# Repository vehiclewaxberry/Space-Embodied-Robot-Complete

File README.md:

# 航天服务星具身智能机械臂机器人

**Space Service Robot with Embodied Intelligence**

面向在轨服务的 12U 立方星服务星 + B601 六自由度机械臂的完整数字样机、机械/电气设计与自由漂浮动力学证据库。

*A complete digital prototype, mechanical/electrical design package, and free-floating dynamics evidence base for a 12U CubeSat servicing spacecraft with a B601 6-DOF manipulator.*

---

## 项目定位 / Scope

这是一个**在轨服务空间机器人学的科研项目**，同时承载长期硬件研发。两条线互为约束：

- **研究线** —— 面向抓取后可稳定性的**预见式具身抓取**。核心问题：在自由漂浮、刚柔耦合、目标非合作的条件下，捕获策略的可行域由哪些物理边界决定。
- **工程线** —— 可装配、可参数化、可验证的 12U 服务星与 B601 机械设计，作为研究结论的物理载体与参数来源。

研究产出以**机器裁决证据**（`*_gate_check.json`）与论文结构为组织形式，而非演示件。论文规划入口见 [`10_research/paper1_architecture.md`](10_research/paper1_architecture.md)（Paper 1 = 柔性耦合捕获任务可行域），问题树见 [`10_research/research_questions/`](10_research/research_questions/)。

*This is a research project in on-orbit-servicing space robotics, carried alongside long-term hardware development. The research line studies predictive embodied grasping for post-capture stabilizability — specifically, which physical boundaries determine the feasible domain of capture strategies under free-floating, rigid-flexible coupled, non-cooperative conditions. Outputs are organised as machine-adjudicated evidence and paper structure, not demos.*

> **关于历史来源**：项目起源于中国研究生未来飞行器创新大赛（第十二届）。比赛记录、机器 Gate 与负结果作为**历史证据**原位保留，但**比赛期限与比赛交付不再构成研究议程、工程验收门槛或授权 Gate**。请勿据历史比赛记录升级当前结论。

### 任务设定 / Mission

| 项 | 值 |
|---|---|
| 服务星 | 12U CubeSat 平台 |
| 机械臂 | B601，6R 串联构型 |
| 目标 A | 150 kg 翻滚空间碎片 |
| 目标 B | 22 kg 非合作目标星 |
| 动力学工况 | 自由漂浮（free-floating），基座不固定 |
| 研究线 | 面向抓取后可稳定性的预见式具身抓取 |

---

## 仓库导航 / Repository layout

八个业务域，根目录不再建立平行的 `src/` `docs/` `results/` 树。

| 目录 | 内容 |
|---|---|
| [`01_project/`](01_project/) | 项目入口、治理、协作原件、历次工作包记录 |
| [`10_research/`](10_research/) | 研究问题树、方法、合同、知识库、论文材料 |
| [`20_engineering/`](20_engineering/) | **CAD、电气、BOM、参数、接口与设计证据** |
| [`30_simulation/`](30_simulation/) | 模型、程序、测试、原始结果、机器裁决 |
| [`40_evidence/`](40_evidence/) | 图表、媒体、离线展示 |
| [`50_literature/`](50_literature/) | 题录、阅读卡、BibTeX |
| [`70_tools/`](70_tools/) | 编目、展示、校验工具 |
| [`80_third_party/`](80_third_party/) | 外部来源登记与许可（见 [NOTICE.md](NOTICE.md)） |

全项目导航入口：**[PROJECT_MAP.md](PROJECT_MAP.md)**

---

## 协作者快速上手 / Getting started for collaborators

仓库含 **13 GB Git LFS 内容**（7,328 个对象，主要是 CAD）。**克隆方式选错会出问题**，请按下面来。

### ① 先装 Git LFS —— 不装的话你拿到的是一堆占位符

这是最常见的坑：没装 LFS 就 `git clone`，所有 CAD 文件会变成约 130 字节的指针文本。**文件名看着都在，但一个都打不开。**

```bash
git lfs install
```

*Install [Git LFS](https://git-lfs.com/) first. Without it every CAD file clones as a ~130-byte pointer stub — the filenames all look right, but nothing opens.*

### ② 推荐：先不拉 CAD，按需取件

完整克隆会下载 13 GB，**消耗仓库的 LFS 带宽配额**；配额耗尽后**所有人**的 LFS 下载都会被阻断。除非确实需要全部 CAD，否则请用：

```bash
GIT_LFS_SKIP_SMUDGE=1 git clone https://github.com/vehiclewaxberry/Space-Embodied-Robot-Complete.git
```

这样能拿到全部代码、文档、仿真结果与机器裁决（约 256 MB），CAD 先留作指针。需要某个具体部件时再单独拉：

```bash
# 例：只取最新整星总装
git lfs pull --include="20_engineering/SERVICE_STAR_CORE_INSTALLATION_R6H_20260920/**"

# 例：只取某一批 STEP
git lfs pull --include="20_engineering/SERVICE_STAR_HARDWARE_COMPACT_20260921/**"
```

*Full clones pull 13 GB and consume the repository's shared LFS bandwidth quota; once it is exhausted, LFS downloads are blocked for everyone. Prefer the skip-smudge clone above and fetch only what you need.*

### ③ 确实需要全部 CAD 时

```bash
git clone https://github.com/vehiclewaxberry/Space-Embodied-Robot-Complete.git
```

请先知会仓库所有者——这一次操作会占用约 13 GB 带宽配额。

### 打开 CAD 需要什么

| 格式 | 仓库内文件数 | 需要的软件 |
|---|---|---|
| `.STEP` | 3,404 | **任意 CAD 软件**（FreeCAD、Fusion、CATIA、NX…）— 没有 SolidWorks 就用这个 |
| `.SLDASM` / `.SLDPRT` | 6,233 | SolidWorks 2024 及以上 |
| `.FCStd` | 89 | FreeCAD |
| `.glb` / `.stl` | 873 | 任意三维查看器（仅可视化，非设计源） |

全部 CAD 合计 13 GB LFS（7,328 个去重对象——同内容的文件共享一份存储，所以实际下载量小于按文件数的估计）。

---

## 研究线 / Research programme

### 六层架构

研究按六层组织，**各层分别取证，不由某层结论覆盖其它层**：

| 层 | 职责 | 状态 |
|---|---|---|
| **L0** | 任务可行性 / 策略 | 已实现（`sim_10`、`sim_12`） |
| **L1** | SAFE 证据核 | `SAFE-00` 47/47 PASS，`review_status=PENDING_REVIEW` |
| **L2** | 确定性控制 | `CTRL-01/02`，带 PROVISIONAL 范围限定 |
| **L3** | 刚柔世界模型 | `sim_11` v1.1，含占位参数 |
| **L4** | 具身候选生成 | 规划态，未实施 |
| **L5** | 地面验证 | H0–H3 规划态，未实施 |

导航：[`10_research/00_project_architecture/`](10_research/00_project_architecture/)

### 论文线

| 论文 | 主题 | 状态 |
|---|---|---|
| **Paper 1** | 柔性耦合捕获任务可行域 | 证据/查新收口中，结构见 [`paper1_architecture.md`](10_research/paper1_architecture.md) |
| **Paper 2** | 接触带宽 / 保真度 | 候选，未启动 |

问题树 Q1–Q6、理论假设与主张-证据关系见 [`10_research/research_questions/`](10_research/research_questions/)、[`theory_graph/`](10_research/theory_graph/)、[`contribution_map/`](10_research/contribution_map/)。

文献主清单：[`50_literature/references/manifest.yaml`](50_literature/references/manifest.yaml)（44 篇 PDF / 29 张阅读卡；**PDF 全文因版权不随仓库分发**，按 manifest 自行获取）。

### 规划态支线（**尚未授权实施**）

`BRIDGE-UT` 带界不确定目标操作、`Q6-L1` 预制接口装配、On-Orbit Assembly Wave A、Physics-Gated Agent、ROM、VLA —— 这些目录存在**不等于**实施完成或已授权。请按各目录内的具名合同理解其范围。

---

## 当前硬件基线 / Current hardware baseline

这是接手后续开发时**首先要看的**部分。

| 要做的事 | 入口 |
|---|---|
| 四系统硬件主设计（机械 / 电气线束 / 能源热控 / 动力推进） | [`20_engineering/SERVICE_STAR_HARDWARE_COMPACT_20260921/`](20_engineering/SERVICE_STAR_HARDWARE_COMPACT_20260921/) |
| **最新整星总装（数字样机）** | [`SERVICE_STAR_CORE_INSTALLATION_R6H_20260920/native/SERVICE_STAR_SERVICE_R6H.SLDASM`](20_engineering/SERVICE_STAR_CORE_INSTALLATION_R6H_20260920/native/) |
| 电气选型当前指针 | [`20_engineering/SERVICE_STAR_ELECTRICAL_LATEST.json`](20_engineering/SERVICE_STAR_ELECTRICAL_LATEST.json) |
| R7 安装布局草案（**未完成项**） | [`20_engineering/SERVICE_STAR_AUX_STOP_INSTALLATION_R7_20260921/`](20_engineering/SERVICE_STAR_AUX_STOP_INSTALLATION_R7_20260921/) |
| 上游机械来源（星体本体） | [`20_engineering/service_robot_wp03_spacecraft_body_r1/`](20_engineering/service_robot_wp03_spacecraft_body_r1/) |

**读法约定**：选型候选与未安装草案分别看待，**不按目录日期推定完工**。R6H 原件保留，没有回退为早期 WP03。

### CAD 格式说明

原生件为 SolidWorks（`.SLDPRT` / `.SLDASM`），中性交换格式为 `.STEP`，二者均通过 Git LFS 存储。**克隆方式与所需软件见上文[协作者快速上手](#协作者快速上手--getting-started-for-collaborators)**——直接 `git clone` 而未装 LFS 会拿到占位符而非真实 CAD。

---

## 已验证的核心结果 / Verified results

以下数值来自各模块的**机器裁决 JSON**（`*_gate_check.json`），引用时请勿改动。注意：**测试 PASS ≠ 科学 Gate PASS**。

| 编号 | 结论 | 关键数值 |
|---|---|---|
| `sim_05` | B601 自由漂浮，臂运动致基座姿态扰动 | 峰值 **19.20°**；动量守恒 7.3e-17 |
| `sim_06` | 矢量式捕获冲量——**捕获 ≠ 消旋** | 碎片 @3°/s → 捕获后 3.06°/s |
| `sim_07` | ANCF 柔性帆板，点捕获激振 vs 刚性锁定 | ≈ **92×**；振铃 37–75 s |
| `sim_08` | 150 kg 碎片消旋**必须用推力器** | `\|H_c\|` = 3.65 N·m·s = **12×** 轮组容量 |
| `sim_10` | 任务可行域 9000 点四门 fail-closed 扫描 | 裁决 `SIM10_GATES_PASS` |
| `sim_11` v1.1 | 刚柔耦合，有限接触窗口 | `SIM11_GATES_PASS_WITH_PROVISIONAL_PARAMS` |
| `sim_12` Phase1 | 16 例策略证明集——**最优捕获策略是 binding gate 的函数** | `SIM12_PHASE1_GATES_PASS` |
| `SAFE-00` | 运行时安全门 | 47/47 PASS，七绕过面全封 |

### 对后续在轨服务开发的直接含义

1. **基座扰动不可忽略**：自由漂浮下 19.20° 的姿态耦合意味着臂规划必须与姿态控制联合求解。
2. **捕获与消旋是两个问题**：捕获冲量不消除目标角动量；150 kg 级目标的消旋超出轮组容量一个数量级。
3. **柔性帆板是激振主源**：点捕获相对刚性锁定放大约 92 倍，接触策略必须考虑帆板模态。
4. **策略选择依赖于约束边界**：不同 binding gate 下最优策略不同（S1 / S3a / ABORT）。

---

## 明确的未完成项与占位参数 / Known gaps

本节是**刻意保留**的。项目约定：负结果、UNKNOWN 与占位参数不得被整理或总结所掩盖。

| 项 | 状态 | 影响 |
|---|---|---|
| **帆板质量 0.348 kg** | **占位值**。真实面密度 2–5 kg/m²，差 5–10 倍 | 真实参数下「柔性反馈可忽略」的结论**可能翻转**。当前最大硬伤 |
| **接触窗口 `T_c` = 20 ms** | `PROVISIONAL`，待 B601 夹爪实测 | 需替换 `scene_A2_capture.yaml` 后重跑带宽口径 Gate |
| 帆板模态参数 | 占位 | 同上 |
| `e15` ANCF 认证 | 交叉求解最大差 5.64% > 5% 门槛 → `REPEAT_ANCF_CERTIFICATION` | 全耦合新模型须重过该 Gate |
| `FLEX` | `UNKNOWN`，不入 `sim_10` 判据 | 可行域为**刚体边界** |
| R7 安装布局 | 草案，未安装 | 不得按日期推定完工 |
| `CTRL-02` 姿态分账 | `PASS_WITH_PROVISIONAL_SCOPE` | 硬件有效稳定性 `NOT_EVALUATED_NO_ACTUATOR_DYNAMICS` |

> 引用控制类结论时必须带限定语：「**在冻结增益与预注册轨迹下**」。

---

## 证据与结论约定 / Evidence conventions

这套约定是项目的核心工程文化，接手者请遵守：

- **科学结论只认机器裁决 JSON**（`*_gate_check.json`），不认文档摘要。
- **测试通过 ≠ 科学 Gate 通过**。
- 每个 `sim_XX` / `eXX` 模块自带 `src/` `tests/` `results/` `docs/`，自包含。
- 失败、`UNKNOWN`、受限结果**留在原拥有者目录**，不被后续工作覆盖。
- 不同模型与版本的结果**不互相覆盖**，导航不汇总为单一通过状态。
- 目录同名、同日期或位于 `archive/` `_work/` **不足以证明文件无用**。

---

## 复现 / Reproducing

各仿真模块自包含。典型流程：

```bash
cd 30_simulation/sim_11_coupled_dynamics
python -m pytest tests/          # 模块测试
python src/run_all.py            # 重跑场景与 Gate
cat results/sim_11_gate_check.json   # 读机器裁决
```

> **注意**：`control_01` / `control_02` 的 `run_all.py` 会**覆写** `results/` 下的 gate JSON。运行前请先 snapshot，运行后 restore。

---

## 第三方 / Third-party

本仓库**不转发**上游第三方代码库。所使用的外部平台（Basilisk、Exudyn、Chrono、SPART、SpaceDyn、Astrobee、OpenVLA、openpi 等）及其许可证登记于 **[NOTICE.md](NOTICE.md)**，请从各自上游获取。

外部参考 CAD 与供应商模型的来源、版本与许可见 [`80_third_party/README.md`](80_third_party/README.md)。

---

## 引用 / Citation

见 [CITATION.cff](CITATION.cff)。

---

## 许可 / License

见 [LICENSE](LICENSE)。第三方组件各自适用其上游许可，见 [NOTICE.md](NOTICE.md)。

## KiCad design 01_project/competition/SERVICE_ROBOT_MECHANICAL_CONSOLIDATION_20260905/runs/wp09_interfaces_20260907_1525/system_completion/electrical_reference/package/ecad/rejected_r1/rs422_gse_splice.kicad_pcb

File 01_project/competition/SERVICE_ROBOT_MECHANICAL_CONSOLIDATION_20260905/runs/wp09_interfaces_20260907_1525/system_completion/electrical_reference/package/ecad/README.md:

# 原生电气接口候选

已实际生成并用 KiCad10.0.6 读取两套原生设计：

- [直流与信号接口系统工程](wp09_system.kicad_pro)、[原理图](wp09_system.kicad_sch)、[真实导出网表](exports/wp09_system.xml)：24个外部边界符号、117端点、47网络。
- [地面RS-422转接板工程](rs422_gse_splice.kicad_pro)、[PCB](rs422_gse_splice.kicad_pcb)、[原理图](rs422_gse_splice.kicad_sch)、[真实导出网表](exports/rs422_gse_splice.xml)：15个焊线/测试焊盘、5个网络。
- [唯一主端点表](MASTER_FROM_TO.csv)、[原23条记录映射](LINEAGE_23.csv)、[现行电气BOM](MASTER_BOM.csv)、[转接板端点明细](RS422_PAD_MAP.csv)。`power/POWER_FROM_TO.csv` 是来源合同，旧 `functional_closure` 是冻结历史；两者不代替本轮主表。

70行是连接合同，包含未绑定逻辑端点。原A05双极回流触点撤销并入A04，A02/A03改GX11CAB A2(+)/A1(-)极性，L01/L02改3英寸短线。S01–S05端到端电气关系保留，实际地面拼接由A_i.1—TP_i.1—B_i.1的同网铜箔承担。主系统图作端到端表达，板级细节由独立PCB网表精确对应，未把三段实体导体谎报成单根可下料导线。

**这是外部接口设计，不是整机完整制造线束或市电电源柜电路。**PS1只画直流输出边界；市电入口、PE保护连接、壳体及端子防护要由完整GSE责任件实现。DM的VCC_REF/RET_REF/CANH_REF、分线板/USB-CAN逻辑端口、STOP_CONTROL/STOP_MONITOR及未定PV支路不是猜出的物理针脚。它们均不得按图直接压接。明确NC及不宜画成导线的8项要求保存在 [EXCLUDED_REQUIREMENTS_AND_NC.json](EXCLUDED_REQUIREMENTS_AND_NC.json)。RBF电阻、金属接地罩、PGND断路与部署开关仍须实现，未被主表中的逻辑连接替代。

## 实际检查结果

|对象|本轮结果|解释|
|---|---|---|
|系统网表↔主表|70行逐端点通过；117端点的47个连通分区完全一致|不是只比网络名称。|
|系统端点图|原始主表和KiCad实际导出网表均通过|Q/K四状态检查；理想U1穿通模型只用于拓扑。|
|独立反例|22/22通过；对实际导出网表另加PDU9–10短接也被拒绝|涵盖保护旁路、回流缺失、跨域、USB回灌、双源并接、伪批准和误标签。|
|系统ERC|1项error，0 warning|U1.IN+跨被动保护/切断器边界没有驱动电源声明；保留，不使用PWR_FLAG或排除规则。停止/回生硬件仍开放。|
|RS422板ERC|0违规|板本来就是5条无源导体，非把有源部件伪设passive。|
|RS422板DRC|0违规、0未布线、0板图一致性违规|包括原生PCB与原理图的值、属性、网络校对。保留工具默认忽略项，不称全制造规则认证。|
|OreSat上游主图/板|ERC11 warnings；DRC2 courtyard errors及其他warnings|真实负结果保留，不能继承上游PASS。|

机器结果：[ECAD_VERIFICATION](../results/ECAD_VERIFICATION.json)、[独立反例](../results/ECAD_SYSTEM_GRAPH_TESTS.json)、[KiCad真实命令](../results/KICAD_RUN.json)。初始排版格点、PCB语法和丝印/属性问题的失败输出保存在 `rejected_r0/`、`rejected_r1/`，后续报告不覆盖其身份。原24项物理检查仍在父本原文件中为NOT_EXECUTED。

## 地面板的机械责任

板外廓40×30 mm，标称总厚1.6 mm；10个Ø1.2 mm焊线孔、5个Ø0.7366 mm测试孔，孔位见PAD_MAP。KiCad `--board-only` 实际输出的基材厚度为**1.51 mm**，不含铜层、阻焊与端接；因此原生SolidWorks板件也是40×30×1.51 mm基材，不冒充完整1.6 mm成品。板件STEP由原生PCB直接导出，冷重开1实体、STEP往返差集体积为0，详见 [NATIVE_BOARD_MATERIAL](../results/NATIVE_BOARD_MATERIAL.json)。[SolidWorks板件](../mechanical/native/RS422_GSE_SPLICE_BOARD.SLDPRT)、[STEP](../mechanical/RS422_GSE_SPLICE_BOARD.step)。它是外部台架件，没有装入705组件整星。

上游测试孔铜箔/钻孔保留，参考丝印由0.56改1 mm并移到孔外2 mm处。新焊线孔、走线、板边和接线标识由本项目负责。每条走线30 mm、宽0.5 mm；无PE/屏蔽搭接、无附加端接电阻。实际FTDI修订/终端、剥线直径与绝缘、焊后清洁/固定、线束卸载和绝缘罩尚未验证。导线不能把拉力直接交给焊盘。默认没有Gerber、充压、带电或制造放行。

复算：在本候选目录运行 `python -X utf8 tools/verify_ecad.py`；原生工具检查用 `tools/run_kicad.py`（脚本会生成候选检查输出，不运行硬件）。源修改见 `tools/build_ecad.py`。BOM中actual_received均为UNCONFIRMED，不推断用户已经购买。

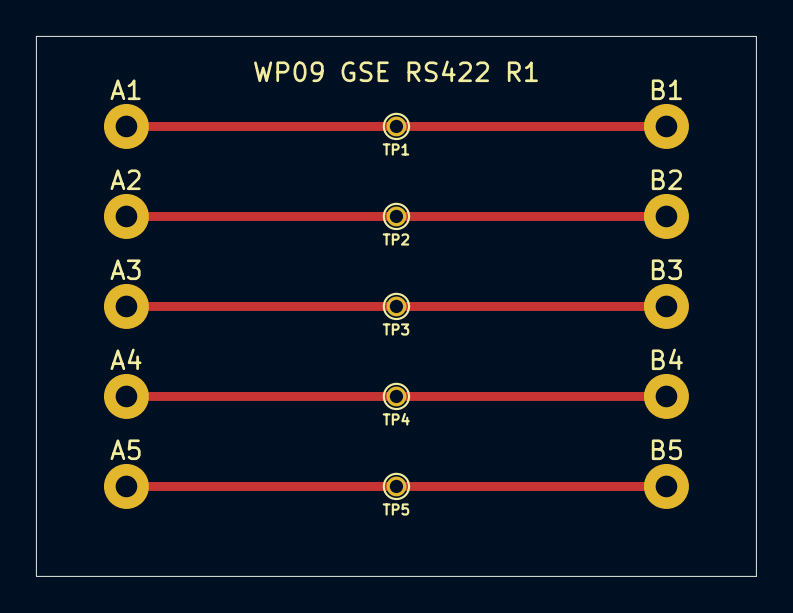
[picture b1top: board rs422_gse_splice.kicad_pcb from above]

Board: 2 copper layers, 40.0 x 30.0 mm, 15 parts (0 on the bottom side), 5 nets.

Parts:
A1, A2, A3, A4, A5: WirePad_GSE
B1, B2, B3, B4, B5: WirePad_GSE
TP1, TP2, TP3, TP4, TP5: TestPoint-MinTH

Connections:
RS_LOOP_1: A1.1, B1.1, TP1.1
RS_LOOP_2: A2.1, B2.1, TP2.1
RS_LOOP_3: A3.1, B3.1, TP3.1
RS_LOOP_4: A4.1, B4.1, TP4.1
RS_LOOP_5: A5.1, B5.1, TP5.1

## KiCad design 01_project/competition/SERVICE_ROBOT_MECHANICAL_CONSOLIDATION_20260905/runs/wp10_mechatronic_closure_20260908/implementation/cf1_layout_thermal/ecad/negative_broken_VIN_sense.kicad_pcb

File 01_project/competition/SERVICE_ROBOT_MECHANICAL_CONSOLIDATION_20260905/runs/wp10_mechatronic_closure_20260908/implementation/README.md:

# 当前可查看候选：V30（2026-09-11）

端接、绝缘盖与局部导线已纳入本候选和总 BOM。查看 [V30 报告](coupled_closure/REVIEW_V30.html)。整机热、布局及推进接口仍开放；旧 V29 选型 BOM 已留存历史，不将旧包哈希套用到现行追加 BOM。

> 当前工作入口：[V29 端接与载板改件](coupled_closure/REVIEW_V29.html)。211位号/677针脚记录，整机仍未闭环；下列旧版发布信息按其原版本理解。

# WP10 最新联合候选（2026-09-10）

从[电气—热控—推进联合查看页](coupled_closure/REVIEW.html)、[完整报告](coupled_closure/README.md)与[候选增量包](coupled_closure/WP10_COUPLED_CANDIDATE.zip)进入。输入来自V26电气/PCB与V21的974实例计划；43个决定性来源文件锁定。已统一207位号/673针脚网络，完成跨相位电热预算、有限推进脉冲边界检查和两套局部参数化STEP，35项针对性测试通过。

局部机械设计共8种项目零件、17个有效实体；候选整机位置经25份真实STEP的窄相位检查三态各18处交叠，已拒绝，尚未装入974实例整机。连续运行热分析发现超限，实际推进ICD、任务工况与整机逐link物性仍待绑定。[本次机器状态](coupled_closure/DELIVERY_STATUS.json)明确保留整机未闭环；未制造、上电或授予飞行信用。下方V18说明为历史入口，不代表最新版本。

---

# WP10 V18 历史：CHB 输入端接板与固定实体

同一候选新增5个安装实例，三态源清单970行，原965行保持。新板DRC0错误/0警告，铜路6检查/7反例和3项实体参数扰动通过；11件局部装配可查看。

- [查看本轮设计与图像](REVIEW.html)
- [原生CHB PCB](ecad/wp10_chb_input.kicad_pcb) / [实际铜图PDF](review/CHB_INPUT_LAYOUT_V18.pdf)
- [11件局部STEP](mechanical/chb_input_assembly.step) / [970行源清单](mechanical/CHB_INPUT_INSTANCE_PLAN.json)
- [设计说明与剩余工作](docs/hardware/CHB_INPUT_V18.md) / [独立只读复核](results/CHB_INPUT_READONLY_REVIEW_V18.json)
- [原37行责任表](SYSTEM_CLOSURE_MATRIX.csv) / [机器裁决](results/DELIVERY_DECISION.json)

整机设计仍开放。C203原板12项DRC、实际配对导线/保持、主馈和使能回线、保护配合、电池/PMM、停止回生/热动态及推进ICD未完成。本轮没有生成970件完整原生SolidWorks总装，也未获制造、上电或飞行放行。

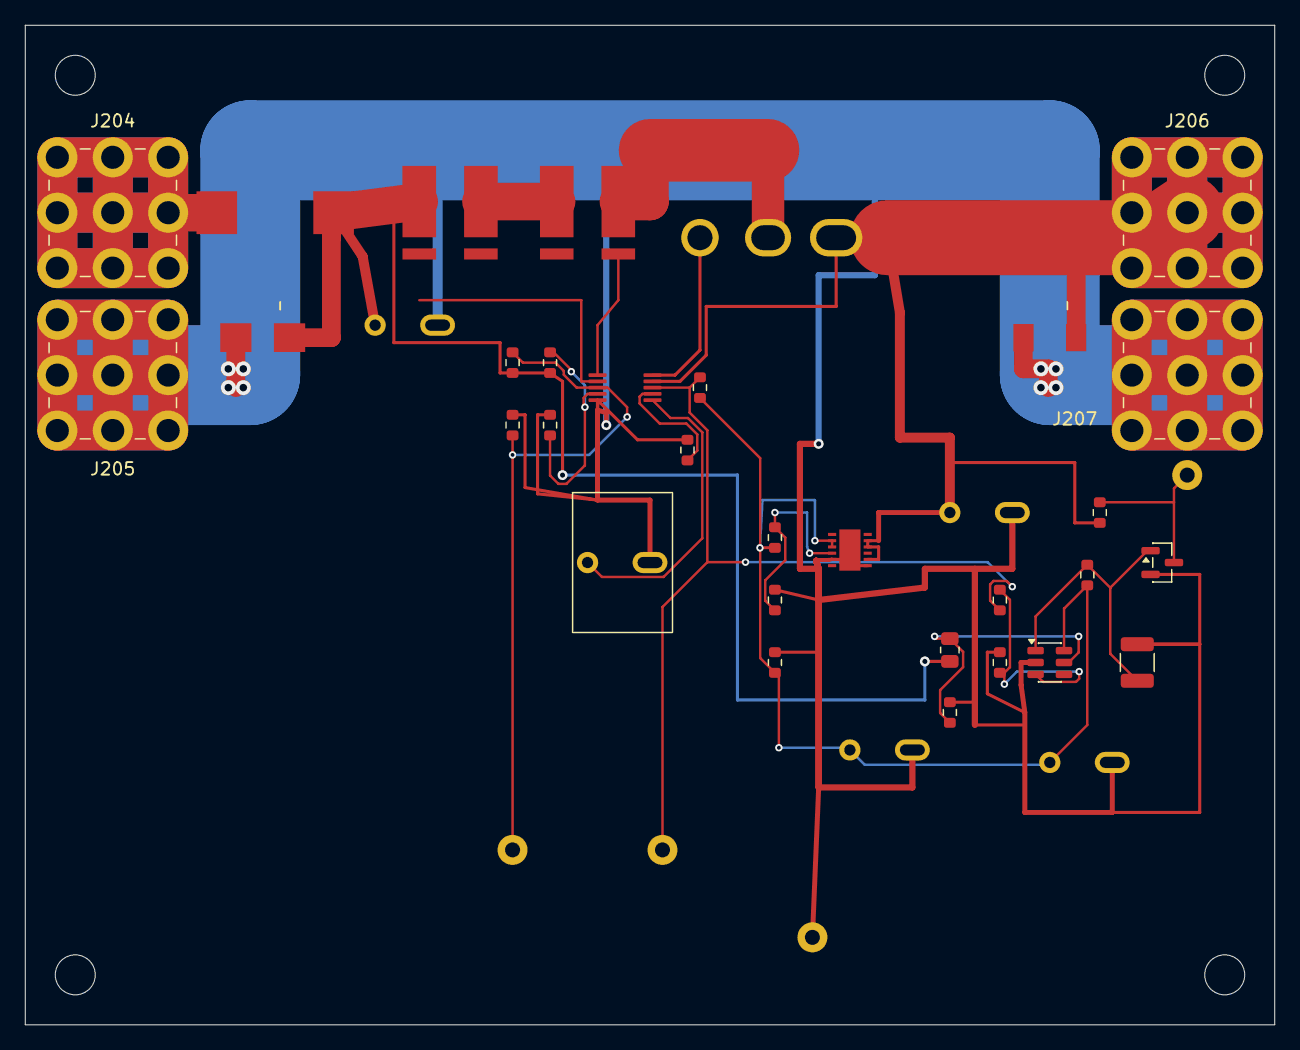
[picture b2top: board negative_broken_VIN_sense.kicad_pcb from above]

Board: 2 copper layers, 100.0 x 80.0 mm, 43 parts (0 on the bottom side), 18 nets.

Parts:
C201: MKP2C041001N00JSSD; C201_MKP2_1uF_P5_Slot2
C202, C213: MKP2D031001F00JSSD; MKP2_D031001F00_P5_Slot2
C211: MKS2D041501M00JSSD; MKS2_D041501M00_P5_Slot2
C212: MKS2D044701O00JSSD; MKS2_D044701O00_P5_Slot2
D201: SMBJ30A-13-F; SMBJ30A_A1K2
D202: STPS3H100U; STPS3H100U_A1K2
F201: 1025HC30-RTR; Fuse_Eaton_1025HC_20to30A_3p25x3p43_P9p35
J204, J205, J206, J207: 74651195R; MP_Wurth_WP-THRSH_74651195R
MH1, MH2, MH3, MH4: (no value)
PORT_ENABLE: PROJECT_WIRE_LANDING_NOT_OEM_CONNECTOR
PORT_PGD: PROJECT_WIRE_LANDING_NOT_OEM_CONNECTOR
PORT_RESET: PROJECT_WIRE_LANDING_NOT_OEM_CONNECTOR
PORT_SIGNAL_RETURN: PROJECT_WIRE_LANDING_NOT_OEM_CONNECTOR
Q201: IXTH75N10L2; IXTH_TO247_G1D2S3_P5p45_Slots
Q204: 2N7002K-7; SOT-23
R201: WSLP27262L000FEA; WSLP2726_KelvinSplit_TwoTerminals
R202: WSLP2726L2000FEA; WSLP2726_KelvinSplit_TwoTerminals
R203: TNPW060347K5BEEA; R_0603_1608Metric
R204: TNPW06035K90BEEA; R_0603_1608Metric
R205: TNPW0603120KBEEA; R_0603_1608Metric
R206, R212, R216: TNPW060310K0BEEA; R_0603_1608Metric
R207: TNPW060330K1BEEA; R_0603_1608Metric
R211: TNPW060338K3BEEA; R_0603_1608Metric
R213: TNPW06034K70FEEA; R_0603_1608Metric
R214: TNPW06033K48BEEA; R_0603_1608Metric
R215: TNPW0805374KBEEA; R_0805_2012Metric
R217: TNPW060333K0FEEA; R_0603_1608Metric
R218: TNPW12102M20FEEA; R_1210_3225Metric
R219: TNPW0603100KFEEA; R_0603_1608Metric
R220: TNPW060310K0FEEA; R_0603_1608Metric
R221: TNPW0603100RFEEA; R_0603_1608Metric
U201: LM5069MM-1; LM5069_DGS10_P0p5_NoEP
U205: LT3013EDE#PBF; LT3013_DE12_EP13_3x4_Pin1LeftTop
U206: TPS3808G01DBVR; SOT-23-6

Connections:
WP10_BAT_PROTECTED_PLUS: F201.1, J204.1
WP10_CHB_ENABLE: PORT_ENABLE.1, Q204.3, R219.2
WP10_CHB_ENABLE_GATE: Q204.1, R217.2, R218.1, U206.1
WP10_HS_OVLO: R205.2, R206.1, U201.4
WP10_HS_PGD: PORT_PGD.1, R214.2, R221.1, U201.8
WP10_HS_POWER_LIMIT: R207.1, U201.7
WP10_HS_TIMER: C201.1, U201.6
WP10_HS_UVLO: PORT_RESET.1, R203.2, R204.1, U201.3
WP10_INPUT_RETURN: C201.2, C202.2, C211.2, C212.2, C213.2, D201.1, D202.1, J205.1, J207.1, PORT_SIGNAL_RETURN.1, Q204.2, R204.2, R206.2, R207.2, R212.2, R213.2, R216.2, R218.2, R220.2, U201.5, U205.5, U205.7, U205.13, U206.2
WP10_MAIN_FUSED: C202.1, D201.2, F201.2, R201.1, R203.1, R205.1, R215.1, U201.2
WP10_MAIN_GATE: Q201.1, U201.10
WP10_MAIN_SENSE: Q201.2, R202.2, U201.1
WP10_PRECHARGED_PLUS: C211.1, D202.2, J206.1, Q201.3, R219.1, U201.9, U205.8, U205.10, U205.11
WP10_SENSE_MID: R201.2, R202.1
WP10_STARTUP_ADJ: R211.2, R212.1, U205.4
WP10_STARTUP_BIAS: C212.1, C213.1, R211.1, R213.1, R214.1, R217.1, U205.2, U205.3, U206.6
WP10_STARTUP_INPUT_SENSE: R215.2, R216.1, U206.5
WP10_STARTUP_PG_RECEIVER: R220.1, R221.2, U206.3

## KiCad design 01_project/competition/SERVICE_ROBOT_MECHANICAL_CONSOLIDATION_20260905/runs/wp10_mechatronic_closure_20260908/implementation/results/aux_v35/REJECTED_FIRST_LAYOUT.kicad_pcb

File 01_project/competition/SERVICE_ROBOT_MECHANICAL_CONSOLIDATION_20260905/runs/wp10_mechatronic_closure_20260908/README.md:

# WP10 机电设计补全与研究交接

**现在还不能完整交付可装配工程样机的全部机电设计。可以进入模型建立与验证、理论和算法研究准备，并让动力学需求反向支撑机电收束。** 当前873构型尚不能作为已验证的真实硬件数字身体，用于宣称控制或RL性能。

[统一查看页](REVIEW.html) · [机器判定](results/DELIVERY_DECISION.json) · [完整工作包状态](SYSTEM_CLOSURE_MATRIX.csv) · [机电与研究共同输入](ENGINEERING_RESEARCH_LOOP_ZH.md)

## 本轮真正完成的设计工作

- 停止电路从71增至76器件，接入TSR1-2433/2450辅助供源、24Ω/39Ω预负载及TC4420CAT驱动。实际子页234已接脚/40网，440项设计检查、494项独立检查通过，范围为0–50°C地面静态候选。已关闭原UCC输入电流上界未知这一局部问题。
- 修订系统原理图包含99器件/97网、72条外部接线；194项网表与身份检查通过。BOM为107行，99个实际ref一一对应。J101.1/.2是内部电源测试端，禁止接外部供源。
- 从873实例/43owner构建三态SI参数入口，实际核对1081份几何文件SHA，完成25146项来源/坐标检查，以及31项单位、惯量和记账测试（其中包含负控）。
- 完成237份唯一STEP源、306个材料模型实例的质量/质心/惯量提取，提供三态SI参数及材料部分汇总；部分质量约7.872303 kg，不是整星质量。结果见[材料模型惯性补充](mechanical_inertia/README_ZH.md)。它是模型计算，不是实测；不会把整臂参考质量或设备包络配成实心。结果交付为SI参数文件，本轮未写回SLDPRT材料/质量属性，原生总装仍使用封存版本。
- 核对26份研究来源及107条历史raw SHA：78匹配、29漂移。旧结果仍可分析，当前目录不能据旧PASS宣称全部精确复现。文档合同120项检查与15个负控只证明合同和证据身份。

[两页实际电气原理图](ecad/exports/WP09_SYSTEM_AND_STOP.pdf) · [可编辑KiCad](ecad/wp09_system.kicad_sch) · [主接线表](ecad/MASTER_FROM_TO.csv) · [分层BOM](ecad/MASTER_BOM.csv) · [电路计算与限制](electrical/README.md)

计数说明：76个停止子页位号包含71个选型器件和5个逻辑接口；99个位号还包含23个顶层设备/边界。97个导出网络含16个显式NC隔离网（其余81个为非NC网络）。它们是原理图统计，不是已装配实物数量。

## “完整交付”还差什么

仍有23项开放工作包，包含真实内部设计责任，不只是到货后实测：星上高功率充电/BMS/均流/热、推进受控ICD与任务分配、逐运动link物性和驱动能力、完整线束/太阳翼连接/承托、PCB与停止动态/反馈，以及整机热/强度/连续运动。

辅助电源的DC恢复裕度约15.7/13.5mV，原厂纹波只有典型值；Schmitt输入跨整个供电域的阈值保证、棕断/启动/瞬态、布局散热和100ms完整停止链仍未证实。保留2项保护/开关后源节点的ERC诊断，已单列[解释](ecad/ERC_DISPOSITION.json)，不靠供源标志或忽略规则清零，也不以ERC数量代替功能覆盖。

原质量账“400项覆盖”中，390项有逐实例数值，另10项B601连杆只由整臂4.5kg共同覆盖。新增材料模型惯性不能补齐整臂分布、真实设备惯性或运动树。完整模型应按刚性link正确合并，**不是要求将每个螺母都建成独立动力学自由度**。读取时按[统一参数入口](MECHANICAL_PARAMETER_ENTRY.json)绑定原实例清单与新增材料惯性；两种质量算法结果不能相加，其他设备未知项继续保留。

## 可以进入哪一段研究

|阶段|现在的出口|工程结论边界|
|---|---|---|
|1. 模型身份与参数|用本次SI入口建立link/关节/惯量、恢复旧快照或新版本绑定，写出假设与未知|当前873真机预测仍未就绪|
|2. 自由漂浮动力学与控制基准|推导并准备守恒、锁关节/刚化退化和交叉求解验证，随后按明确任务执行|先验证模型与执行器能力，再评价控制性能|
|3. 抓取与避障|准备完整关节/碰撞模型、误差界及确定性规划基线，和接触/柔性研究并行|静态装配或离散无碰不能直接证明动态可执行|
|4. 强化学习|定义观察/候选/奖励/终止、训练测试隔离及消融，待环境合同与基线成立后实施|合成环境结果不改称当前硬件性能，物理约束与失效判据独立评价|

[研究准入报告](research_intake/RESEARCH_READINESS.md)区分旧sim05/10/11/12、R2/E23、Sim13合成与负控证据和当前构型。29处raw SHA漂移不自动推翻旧结果，也不能用规范化哈希代替原始字节；受影响精确复现须先恢复快照或另版验证。

机械与动力学相互提供输入：研究给出反作用、捕获载荷、速度/扭矩/能量与时窗，工程用它们定型连接、驱动、电源和停止/热路径。无需把全部理论研究一直等待到飞行鉴定之后，但也不能把当前机械设计的未知项转写成算法默认值。

## 文件与继承

- [873实例参数包](mechanical_intake/PARAMETER_PACKET.json)、[43模块补全清单](mechanical_intake/OWNER_CLOSURE_WORKLIST.csv)、[跨模型参数表](research_intake/MODEL_PARAMETER_CROSSWALK.csv)。
- [本轮完整ZIP](WP10_ENGINEERING_RESEARCH_INPUTS.zip)：包含本轮设计、SI数据、惯性补充、合同与源记录；父原生CAD单独继承。
- [三态873叶SolidWorks完整包](../wp09_interfaces_20260907_1525/system_completion/mechanical/WP09D_NATIVE_873.zip)、[原生冷读/搬迁回执](../wp09_interfaces_20260907_1525/system_completion/results/NATIVE_DELTA_DELIVERY.json)。
- 父本2669文件已按封存SHA核验，未修改父CAD、科学Gate、URDF或旧结果。本轮只做新目录增量；未启动控制、RL训练、机械动作、上电或推进。
- [最终文件完整性](results/FINAL_INTEGRITY.json)是项目目录中的外层回执，只证明文件与引用完整性，不增加工程放行信用。ZIP内含自己的逐文件SHA清单；为避免循环哈希，不内嵌ZIP自身及外层最终回执。历史原生CAD包和封存父版由项目目录中的独立链接提供，未重复打入本轮ZIP。

需求、设计验证与使用工况确认分别记账的组织依据见[NASA产品实现指南](https://www.nasa.gov/reference/5-0-product-realization/)。本项目没有据此宣称NASA标准符合性或飞行鉴定。

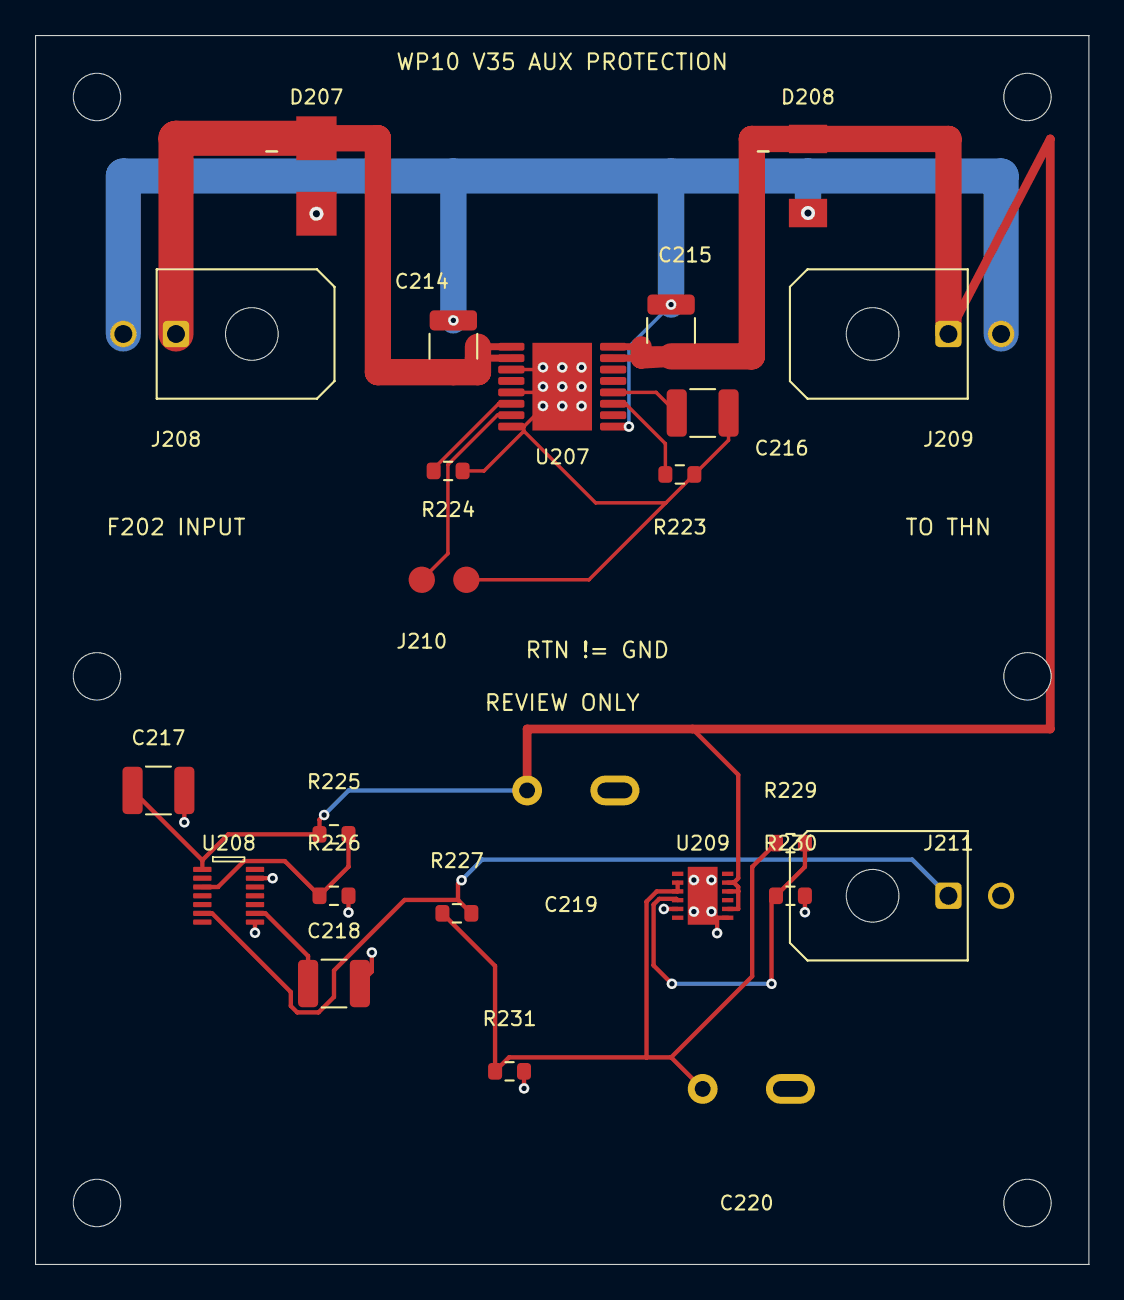
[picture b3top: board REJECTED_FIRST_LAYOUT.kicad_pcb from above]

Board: 2 copper layers, 60.0 x 70.0 mm, 30 parts (0 on the bottom side), 13 nets.

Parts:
C214, C215, C216, C217, C218: 100nF 100V C0G; C_1210_3225Metric
C219: MKS2D041501M00JSSD; MKS2_D041501M00_P5_Slot2
C220: MKS2D044701O00JSSD; MKS2_D044701O00_P5_Slot2
D207: SMBJ30CA-13-F; SMBJ30A_A1K2
D208: STPS3H100U; STPS3H100U_K1A2
J208: 43045-0200 IN; Molex_Micro-Fit_3.0_43045-0200_2x01_P3.00mm_Horizontal
J209: 43045-0200 TO_THN; Molex_Micro-Fit_3.0_43045-0200_2x01_P3.00mm_Horizontal
J210: LOCAL_RESET_TEST_PADS; ResetTestPads
J211: 430450200; Molex_Micro-Fit_3.0_43045-0200_2x01_P3.00mm_Horizontal
MH34_1, MH34_2, MH34_3, MH34_4: M2.5 NPTH 2.7mm; MountingHole_2.7mm_M2.5
MH35_1, MH35_2: MountingHole_2.7mm_M2.5
R223: 5.36k; R_0603_1608Metric
R224: 402k; R_0603_1608Metric
R225: 200k; R_0603_1608Metric
R226, R230: 10k; R_0603_1608Metric
R227: 2.00k; R_0603_1608Metric
R229: 38.3k; R_0603_1608Metric
R231: 4.70k; R_0603_1608Metric
U207: TPS26600PWPR; TPS26600_PWP16_EP17
U208: TPS3760A015DYYR; TPS3760_DYY14
U209: LT3013EDE#PBF; LT3013_DE12_EP13_3x4_Pin1LeftTop

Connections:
WP10_AUX_CTR: C218.1, U208.9
WP10_AUX_DVDT: C216.1, U207.12
WP10_AUX_FUSED: C214.1, D207.2, J208.1, U207.1, U207.2
WP10_AUX_ILIM: R223.1, U207.11
WP10_AUX_LIMITED: C215.1, C217.1, C219.1, D208.1, J209.1, R225.1, U207.15, U207.16, U208.1, U209.8, U209.10, U209.11
WP10_AUX_MODE: R224.1, U207.6
WP10_AUX_PROTECT_RTN: C216.2, J210.2, R223.2, R224.2, U207.3, U207.5, U207.8, U207.17
WP10_AUX_REMOTE_ADJ: R229.2, R230.1, U209.4
WP10_AUX_REMOTE_BIAS: C220.1, R227.1, R229.1, R231.1, U209.2, U209.3
WP10_AUX_RESET: J210.1, U207.7
WP10_AUX_UV_SENSE: R225.2, R226.1, U208.3
WP10_INPUT_RETURN: C214.2, C215.2, C217.2, C218.2, C219.2, C220.2, D207.1, D208.2, J208.2, J209.2, J211.2, R226.2, R230.2, R231.2, U207.9, U208.8, U208.13, U209.5, U209.7, U209.13
WP10_THN_REMOTE: J211.1, R227.2, U208.6

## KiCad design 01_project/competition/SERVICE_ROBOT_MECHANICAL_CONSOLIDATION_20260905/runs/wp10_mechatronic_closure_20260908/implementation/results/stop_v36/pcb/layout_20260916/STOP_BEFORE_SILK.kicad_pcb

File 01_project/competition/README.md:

# 项目工作与历史材料

2026-09-06 整理。目录名保留比赛起源，当前机械工作入口见[工程设计域](../../20_engineering/README.md)，问题与处置见[本轮整理会话](SERVICE_ROBOT_MECHANICAL_CONSOLIDATION_20260905/CURRENT_candidate.md)。比赛期限不是当前工程进度门槛。

| 阅读目的 | 入口与范围 |
|---|---|
| 任务背景、研究问题和 7 月状态差异 | [合并任务知识](../../10_research/knowledge_base/project_context/README.md)；原零基础全景已吸收 |
| 7 月 20 日科学与比赛快照 | [项目现状总览](项目现状总览_20260720.md)；保留机器合同引用的原记录，非现行状态板 |
| 7 月底至 8 月原生机械进展 | [合并历史综述](archive/ROOT_HISTORY_20260729_20260810.md) |
| 7 月研究与文献综合汇报 | [原专题报告](航天工程与空间具身智能机械臂_研究进度与文献综合汇报_20260722.md) |
| R2 来源关系与各轮增量 | [current 来源导航](../current/README_CURRENT.md)；本目录 CURRENT_R2 系列被原始回执逐轮绑定，保留其原字节与日期 |
| 9 月机械输入审阅与实施规划 | [审阅包](PRE_MODE_SWITCH_MECHANICAL_STATE_AUDIT_20260905/)及[实施规划](航天服务星机械设计与装配实施规划_20260905.md)，按各自范围使用 |
| 历史报告与独有载体 | [archive](archive/)；仅作溯源，不自动继承为今天的设计结论 |

研究方法与架构从[研究域](../../10_research/README.md)进入。文档合并保留独有技术、日期和负结果；原始合同、机器 JSON、数据和证据不因叙述重复而删除。

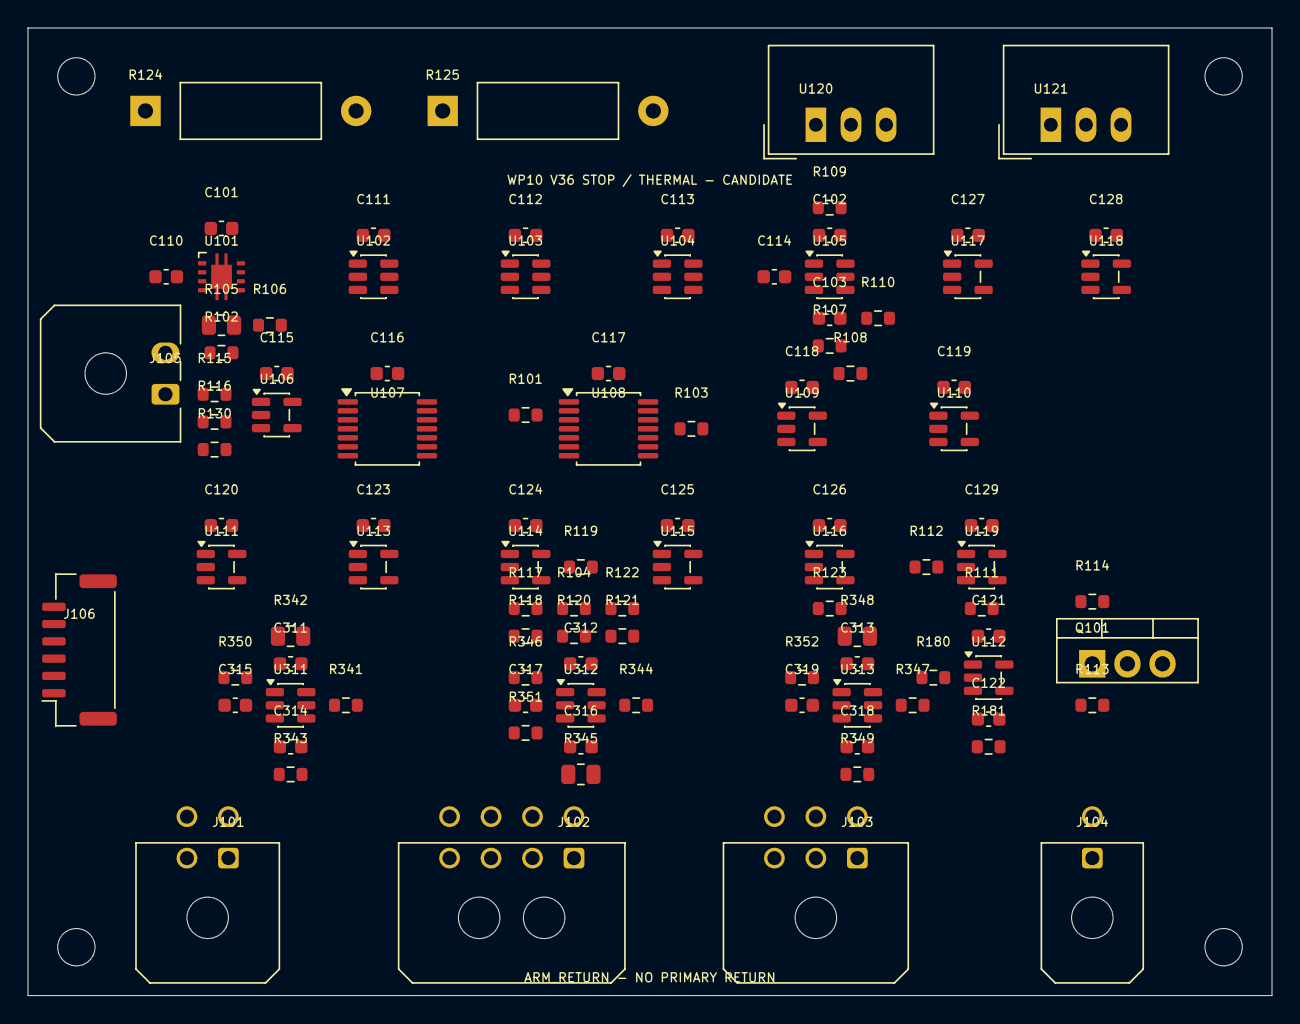
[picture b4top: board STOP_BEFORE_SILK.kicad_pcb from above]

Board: 2 copper layers, 90.0 x 70.0 mm, 107 parts (0 on the bottom side), 49 nets, no tracks yet.

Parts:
C101: C0603C121F5GACTU / C0603C121F5GACTU; C_0603_1608Metric
C102, C103, C122: C0603C105K4RACTU / 1uF X7R 16V 10%; C_0603_1608Metric
C110, C111, C112, C113, C114, C115, C116, C117, C118, C119, C120, C121, C123, C124, C125, C126, C127, C128, C129, C311, C312, C313: C0603C104K3RACTU / 100nF X7R 25V 10%; C_0603_1608Metric
C314, C315, C316, C317, C318, C319: 1nF; C_0603_1608Metric
HSTOP1, HSTOP2, HSTOP3, HSTOP4: M2.5; MountingHole_2.7mm_M2.5
J101: 430450400; Molex_Micro-Fit_3.0_43045-0400_2x02_P3.00mm_Horizontal
J102: 430450800; Molex_Micro-Fit_3.0_43045-0800_2x04_P3.00mm_Horizontal
J103: 430450600; Molex_Micro-Fit_3.0_43045-0600_2x03_P3.00mm_Horizontal
J104: 430450200; Molex_Micro-Fit_3.0_43045-0200_2x01_P3.00mm_Horizontal
J105: 436500200; Molex_Micro-Fit_3.0_43650-0200_1x02_P3.00mm_Horizontal
J106: SM06B-GHS-TB; JST_GH_SM06B-GHS-TB_1x06-1MP_P1.25mm_Horizontal
Q101: IRL630PbF / IRL630PbF; TO-220-3_Vertical
R101: 4.7k; R_0603_1608Metric
R102, R107, R108, R112, R114, R117, R118, R120, R121, R122: CRCW060310K0FKEA / 10k 1%; R_0603_1608Metric
R103, R119, R123: CRCW060347K0FKEA / 47k 1%; R_0603_1608Metric
R104, R116: CRCW06031K00FKEA / 1k 1%; R_0603_1608Metric
R105: TNPW0805510KBEEA / 510k 0.1% 25ppm; R_0805_2012Metric
R106: TNPW060310K0BEEA / 10k 0.1% 25ppm; R_0603_1608Metric
R109, R110: CRCW0603100KFKEA / 100k 1%; R_0603_1608Metric
R111: 100; R_0603_1608Metric
R113: CRCW060322R0FKEA / 22R 1%; R_0603_1608Metric
R115: CRCW060322K0FKEA / 22k 1% 100ppm/C; R_0603_1608Metric
R124: PR02000202409JA100 / 24R 5% 250ppm/C 2W; Vishay_PR02_P15_24
R125: PR02000203909JA100 / 39R 5% 250ppm/C 2W; Vishay_PR02_P15_24
R130: CRCW06033K90FKEA / 3.9k 1% 100ppm/C; R_0603_1608Metric
R180: 10k; R_0603_1608Metric
R181: 47k; R_0603_1608Metric
R341, R344, R347: 8.2k_0.1pct_25ppm; R_0603_1608Metric
R342, R345, R348: 649k_0.1pct_25ppm; R_0805_2012Metric
R343, R346, R349: 100k_0.1pct_25ppm; R_0603_1608Metric
R350, R351, R352: 1k; R_0603_1608Metric
U101: TPS3431SDRBR / TPS3431SDRBR; TPS3431_DRB0008A
U102: TPS3808G33DBVR / TPS3808G33DBVR; SOT-23-6
U103: TPS3808G50DBVR / TPS3808G50DBVR; SOT-23-6
U104: TPS3808G01DBVR / TPS3808G01DBVR; SOT-23-6
U105: SN74LVC2G17DBVR / SN74LVC2G17DBVR; SOT-23-6
U106, U113, U115: SN74LVC1G17DBVR / SN74LVC1G17DBVR; SOT-23-5
U107, U108: SN74LVC74APWR / SN74LVC74APWR; TSSOP-14_4.4x5mm_P0.65mm
U109, U110: SN74LVC1G04DBVR / SN74LVC1G04DBVR; SOT-23-5
U111, U114: SN74LVC1G08DBVR / SN74LVC1G08DBVR; SOT-23-5
U112: UCC27517DBVR; SOT-23-5
U116, U117, U118: SN74LVC1G07DBVR / SN74LVC1G07DBVR; SOT-23-5
U119: SN74LV1T04DBVR; SOT-23-5
U120: TSR 1-2433 / TSR 1-2433; Converter_DCDC_TRACO_TSR-1_THT
U121: TSR 1-2450 / TSR 1-2450; Converter_DCDC_TRACO_TSR-1_THT
U311, U312, U313: TLV6700DDCR; SOT-23-6

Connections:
/Actual watchdog and contactor driver/ARMED: U107.5, U107.12
/Actual watchdog and contactor driver/AUX_CLOSED_3V3: U113.4, U118.2
/Actual watchdog and contactor driver/AUX_DIV: R115.2, R116.1, R130.1
/Actual watchdog and contactor driver/AUX_SENSE: R116.2, U113.2
/Actual watchdog and contactor driver/AUX_STATUS_MCU: J102.6, R122.2, U118.4
/Actual watchdog and contactor driver/BUS_MONITOR_OK: J102.7, R117.1, U114.2
/Actual watchdog and contactor driver/CWD: C101.1, U101.2
/Actual watchdog and contactor driver/EN_STOP: J103.6, R102.1, U101.3
/Actual watchdog and contactor driver/GATE_DRV: R113.1, U112.5
/Actual watchdog and contactor driver/HB_SEEN: U107.2, U108.5
/Actual watchdog and contactor driver/HEARTBEAT_FILTER: R104.2, R119.1, U115.2
/Actual watchdog and contactor driver/HEARTBEAT_IN: J102.1, R104.1
/Actual watchdog and contactor driver/HW_PERMIT_IN: J102.2, R118.1, U114.1
/Actual watchdog and contactor driver/K1_GATE: Q101.1, R113.2, R114.1
/Actual watchdog and contactor driver/MCU_VIO: J102.8, R120.1, R121.1, R122.1
/Actual watchdog and contactor driver/PERMIT_BEFORE_STOP: J103.5, U114.4
/Actual watchdog and contactor driver/RESET_CONTACT: J103.2, R107.1
/Actual watchdog and contactor driver/RESET_EDGE: U105.6, U107.3, U109.2
/Actual watchdog and contactor driver/RESET_N: U109.4, U111.2
/Actual watchdog and contactor driver/RESET_RC: C102.1, R107.2, R109.1, U105.1
/Actual watchdog and contactor driver/RUN_CLEAR_N: U107.13, U111.4
/Actual watchdog and contactor driver/RUN_DRIVE: R111.2, R112.1, U119.2
/Actual watchdog and contactor driver/RUN_INHIBIT_5V: R180.2, U112.4, U119.4
/Actual watchdog and contactor driver/RUN_LATCH: R111.1, R123.1, U107.9, U116.2
/Actual watchdog and contactor driver/RUN_STATUS_MCU: J102.4, R120.2, U116.4
/Actual watchdog and contactor driver/SAFE_N: U106.4, U107.1, U108.1, U111.1, U117.2
/Actual watchdog and contactor driver/SAFE_STATUS_MCU: J102.5, R121.2, U117.4
/Actual watchdog and contactor driver/SENSE_24V: R105.2, R106.1, U104.5
/Actual watchdog and contactor driver/START_CONTACT: J103.4, R108.1
/Actual watchdog and contactor driver/START_EDGE: U105.4, U107.11
/Actual watchdog and contactor driver/START_RC: C103.1, R108.2, R110.1, U105.3
/Actual watchdog and contactor driver/STOP_5V: C111.1, C121.1, C122.1, C129.1, J101.2, R125.1, R180.1, U102.3, U102.6, U103.5, U112.1, U119.5, U121.3
/Actual watchdog and contactor driver/WDI: R103.1, U101.6, U110.2, U115.4
/Actual watchdog and contactor driver/WDI_FALL: U108.3, U110.4
WP10_ARM_RETURN: C101.2, C102.2, C103.2, C110.2, C111.2, C112.2, C113.2, C114.2, C115.2, C116.2, C117.2, C118.2, C119.2, C120.2, C121.2, C122.2, C123.2, C124.2, C125.2, C126.2, C127.2, C128.2, C129.2, C311.2, C312.2, C313.2, C314.2, C315.2, C316.2, C317.2, C318.2, C319.2, J101.4, J102.3, J106.2, J106.4, J106.6, Q101.3, R102.2, R103.2, R106.2, R109.2, R110.2, R112.2, R114.2, R117.2, R118.2, R119.2, R123.2, R124.2, R125.2, R130.2, R181.2, R343.2, R346.2, R349.2, U101.4, U101.9, U102.2, U103.2, U104.2, U105.2, U106.3, U107.7, U108.7, U108.11, U108.12, U108.13, U109.3, U110.3, U111.3, U112.2, U113.3, U114.3, U115.3, U116.3, U117.3, U118.3, U119.3, U120.2, U121.2, U311.2, U312.2, U313.2
WP10_BRAKE_STOP_3V3: C110.1, C112.1, C113.1, C114.1, C115.1, C116.1, C117.1, C118.1, C119.1, C120.1, C123.1, C124.1, C125.1, C126.1, C127.1, C128.1, C311.1, C312.1, C313.1, J101.1, J103.1, J103.3, R101.1, R124.1, R341.1, R344.1, R347.1, U101.1, U101.5, U102.5, U103.3, U103.6, U104.3, U104.6, U105.5, U106.5, U107.4, U107.10, U107.14, U108.2, U108.4, U108.10, U108.14, U109.5, U110.5, U111.5, U113.5, U114.5, U115.5, U116.5, U117.5, U118.5, U120.3, U311.5, U312.5, U313.5
WP10_BRAKE_TEMP_1: J106.1, R341.2, R342.1, R350.1
WP10_BRAKE_TEMP_2: J106.3, R344.2, R345.1, R351.1
WP10_BRAKE_TEMP_3: J106.5, R347.2, R348.1, R352.1
WP10_BRAKE_TEMP_IN_1: C314.1, R350.2, U311.3
WP10_BRAKE_TEMP_IN_2: C316.1, R351.2, U312.3
WP10_BRAKE_TEMP_IN_3: C318.1, R352.2, U313.3
WP10_BRAKE_TEMP_OPEN_1: C315.1, R342.2, R343.1, U311.4
WP10_BRAKE_TEMP_OPEN_2: C317.1, R345.2, R346.1, U312.4
WP10_BRAKE_TEMP_OPEN_3: C319.1, R348.2, R349.1, U313.4
WP10_BRAKE_THERMAL_FAULT_N: R101.2, R181.1, U101.7, U101.8, U102.1, U103.1, U104.1, U106.2, U112.3, U311.1, U311.6, U312.1, U312.6, U313.1, U313.6
WP10_LEGACY_079: J105.2, R115.1
WP10_LEGACY_080: J104.2, Q101.2
WP10_STOP_24V: J101.3, J104.1, J105.1, R105.1, U120.1, U121.1
